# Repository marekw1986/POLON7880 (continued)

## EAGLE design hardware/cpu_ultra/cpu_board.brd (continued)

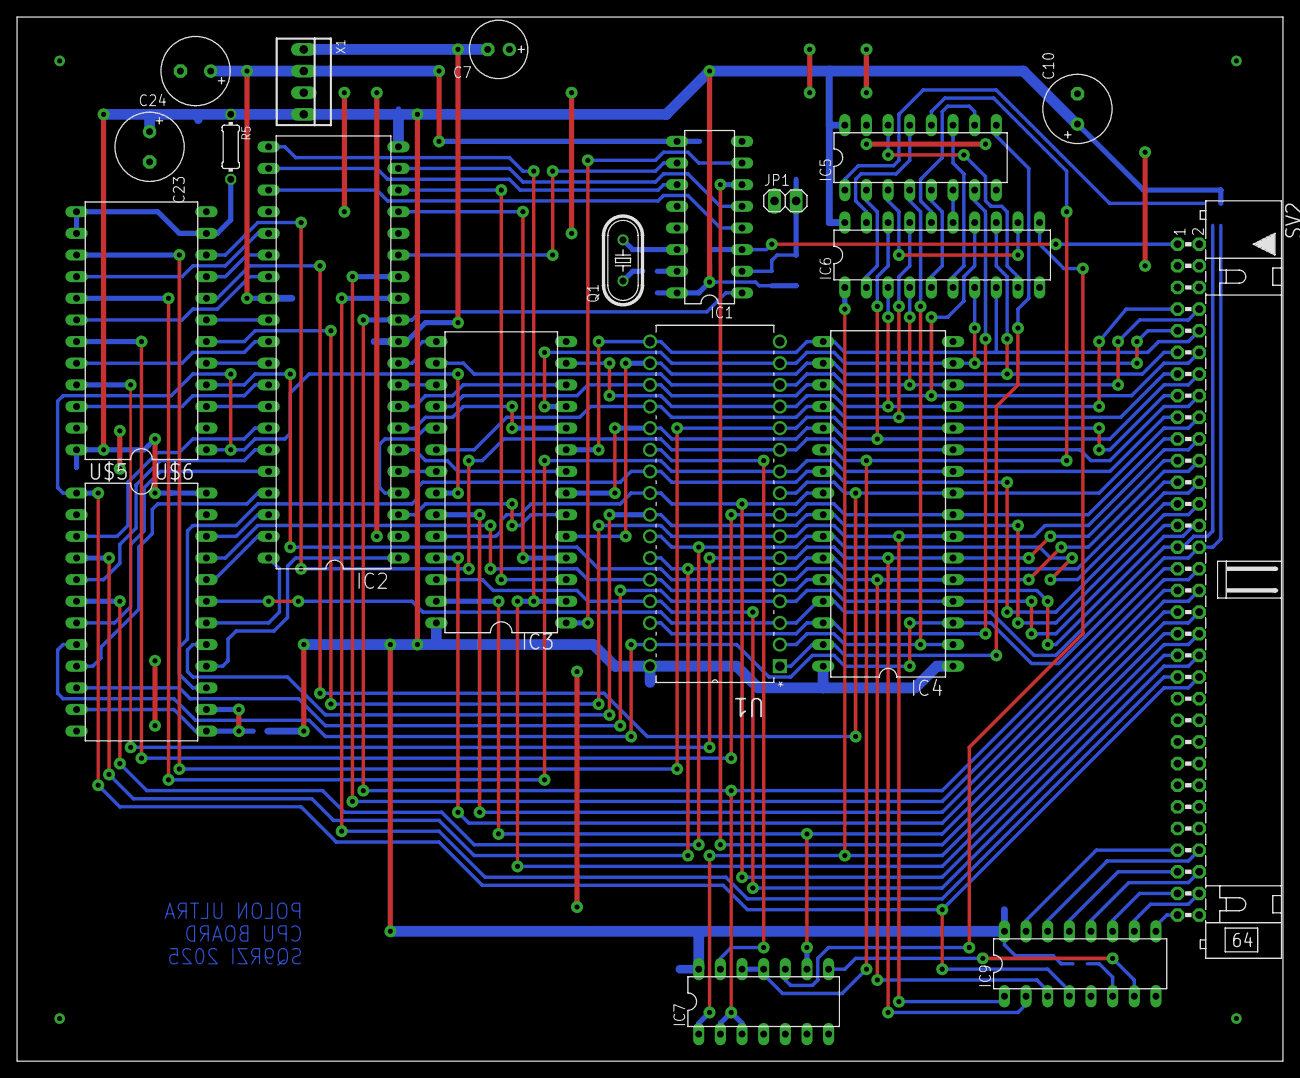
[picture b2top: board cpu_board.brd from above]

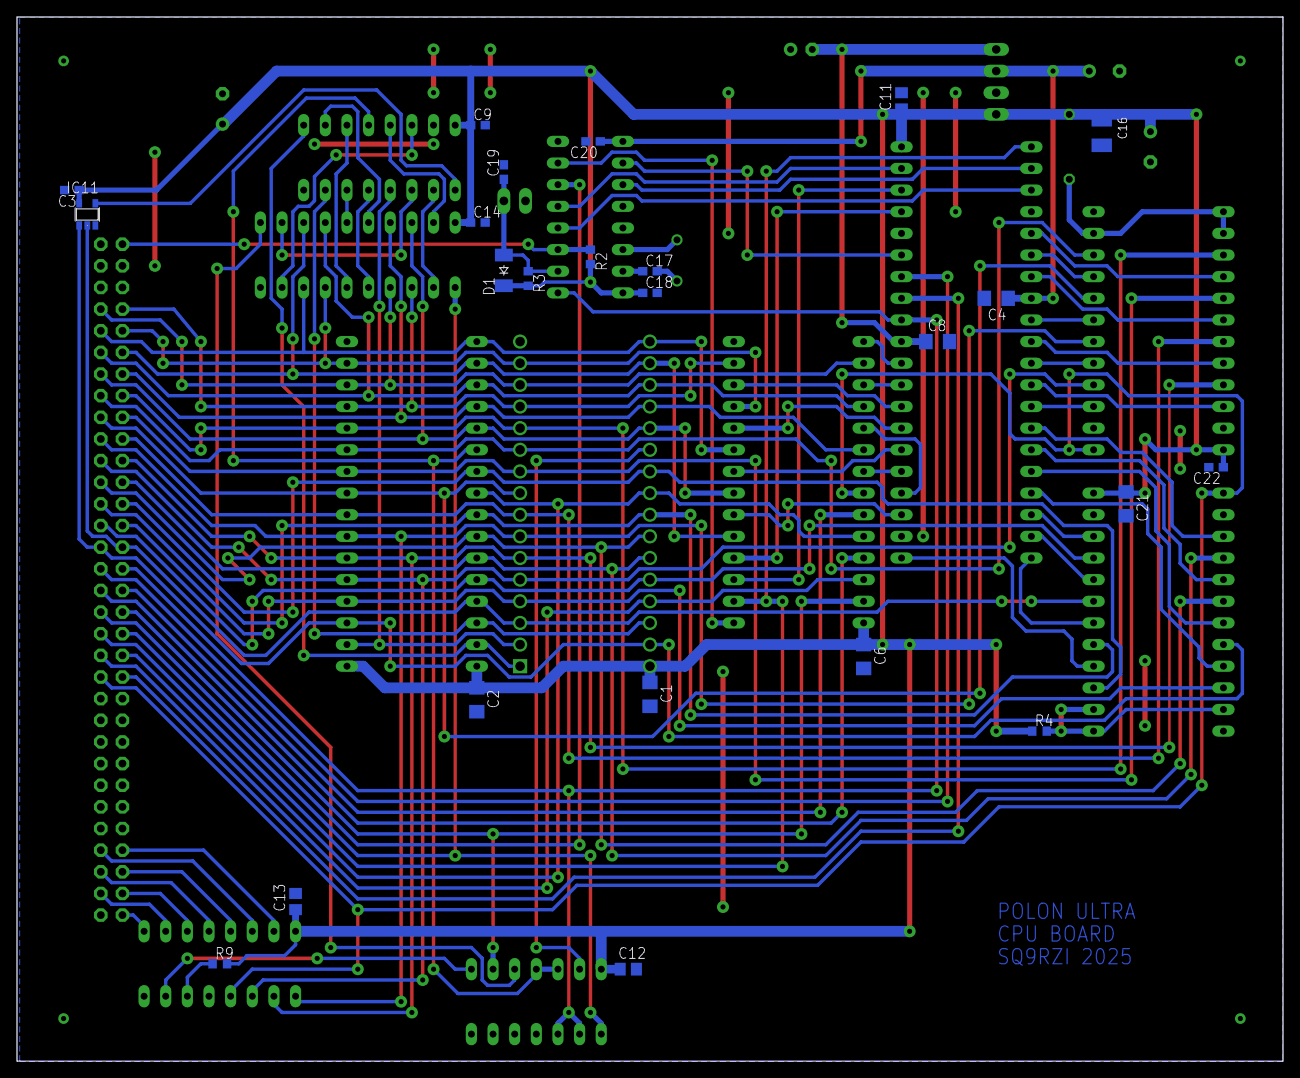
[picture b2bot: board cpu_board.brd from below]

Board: 2 copper layers, 148.6 x 122.5 mm, 44 parts (24 on the bottom side), 102 nets.

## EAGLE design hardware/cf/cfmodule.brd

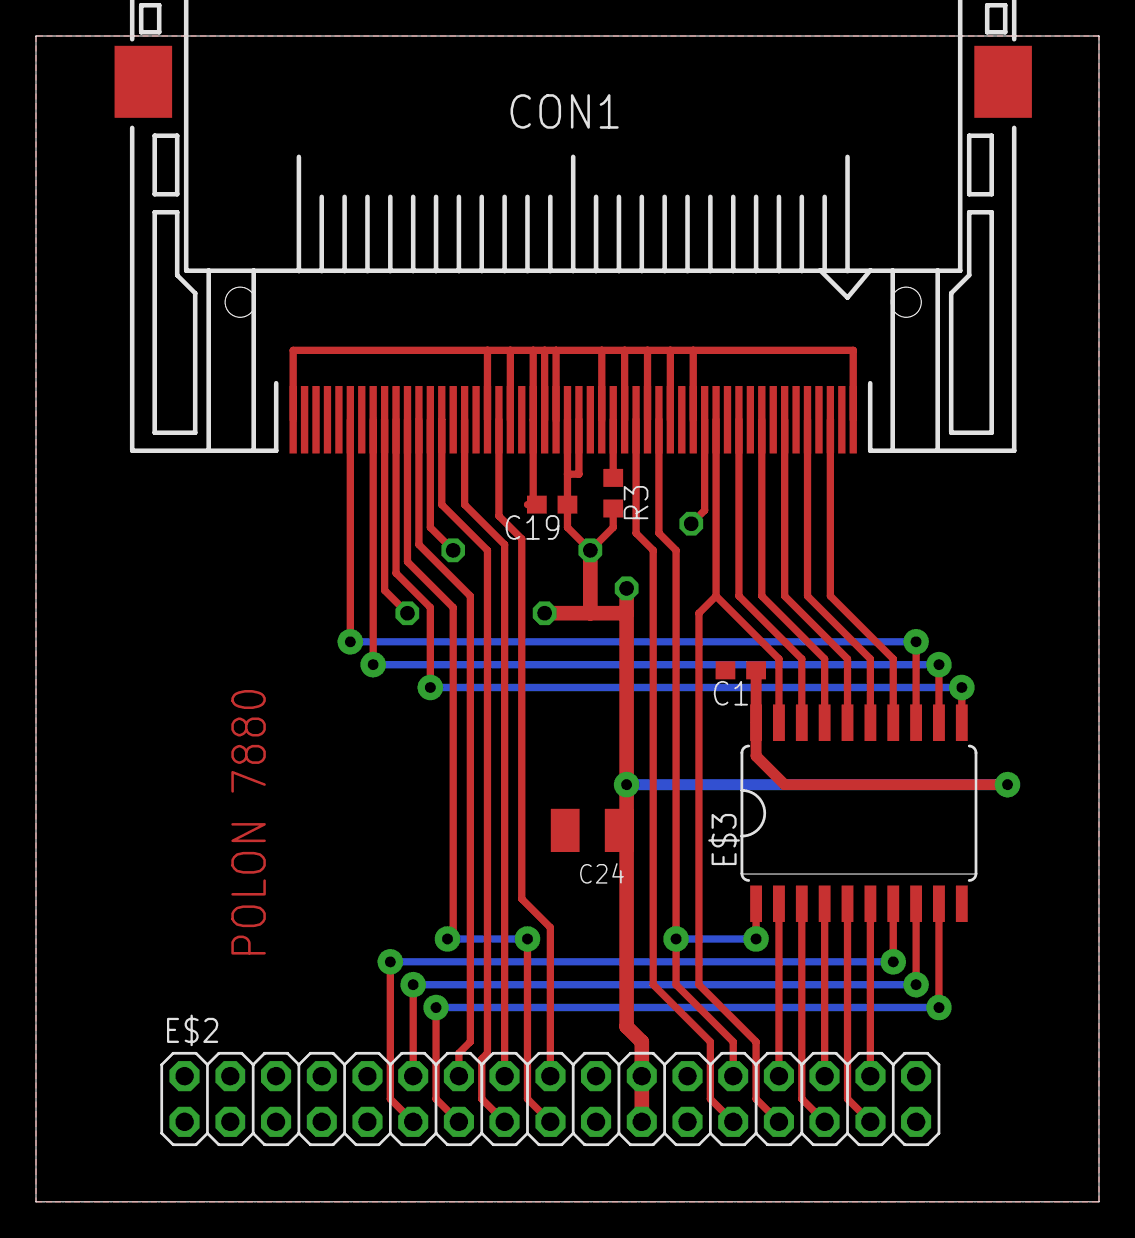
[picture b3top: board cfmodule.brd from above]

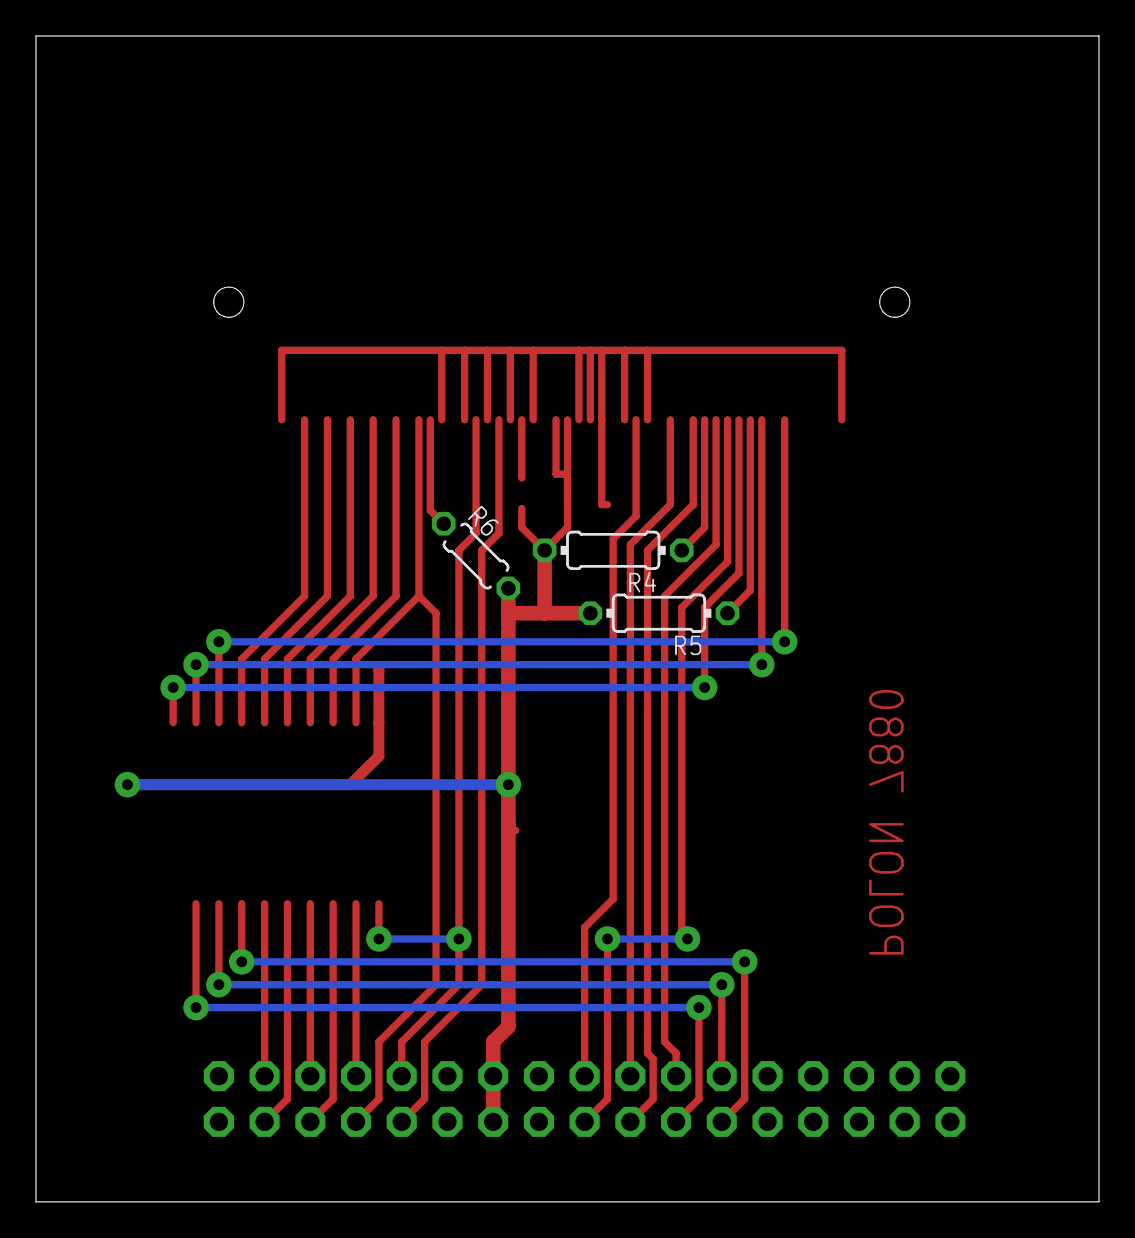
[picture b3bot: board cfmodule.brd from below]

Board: 2 copper layers, 59.1 x 64.8 mm, 10 parts (3 on the bottom side), 30 nets.

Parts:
C1, C19: C0603
C24: SMC_B
CON1: MI20-50PD-SF
E$2: 2X17
E$3: SO20W
R3: R0603
R4, R5: 0204/7
R6: 0204/5

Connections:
A0: CON1.20, E$2.14
A1: CON1.19, E$2.15
A2: CON1.18, E$2.16
CF_CS0: CON1.7, E$2.27, E$3.19
D0: CON1.21, E$3.11
D1: CON1.22, E$3.12
D2: CON1.23, E$3.13
D3: CON1.2, E$3.14
D4: CON1.3, E$3.15
D5: CON1.4, E$3.16
D6: CON1.5, E$3.17
D7: CON1.6, E$3.18
GND: C1.2, C19.2, C24.-, CON1.1, CON1.8, CON1.9, CON1.10, CON1.11, CON1.12, CON1.14, CON1.15, CON1.16, CON1.17, CON1.39, CON1.50, E$2.1, E$2.2, E$2.19, E$2.20, E$2.23, E$2.24, E$2.33, E$2.34, E$3.10
IO_RD: CON1.34, E$2.26, E$3.1
IO_WR: CON1.35, E$2.25
unnamed: CON1.36, R3.1
unnamed: CON1.44, R4.1
unnamed: CON1.46, R5.1
unnamed: CON1.32, R6.1
RST: CON1.41, E$2.18
S$1: E$2.30, E$3.4
S$2: E$2.28, E$3.2
S$8: E$2.13, E$3.9
S$9: CON1.45, E$2.17
S$11: E$2.29, E$3.3
S$12: E$2.31, E$3.5
S$13: E$2.32, E$3.6
S$15: E$2.12, E$3.8
S$16: E$2.11, E$3.7
VCC: C1.1, C19.1, C24.+, CON1.13, CON1.38, E$2.21, E$2.22, E$3.20, R3.2, R4.2, R5.2, R6.2

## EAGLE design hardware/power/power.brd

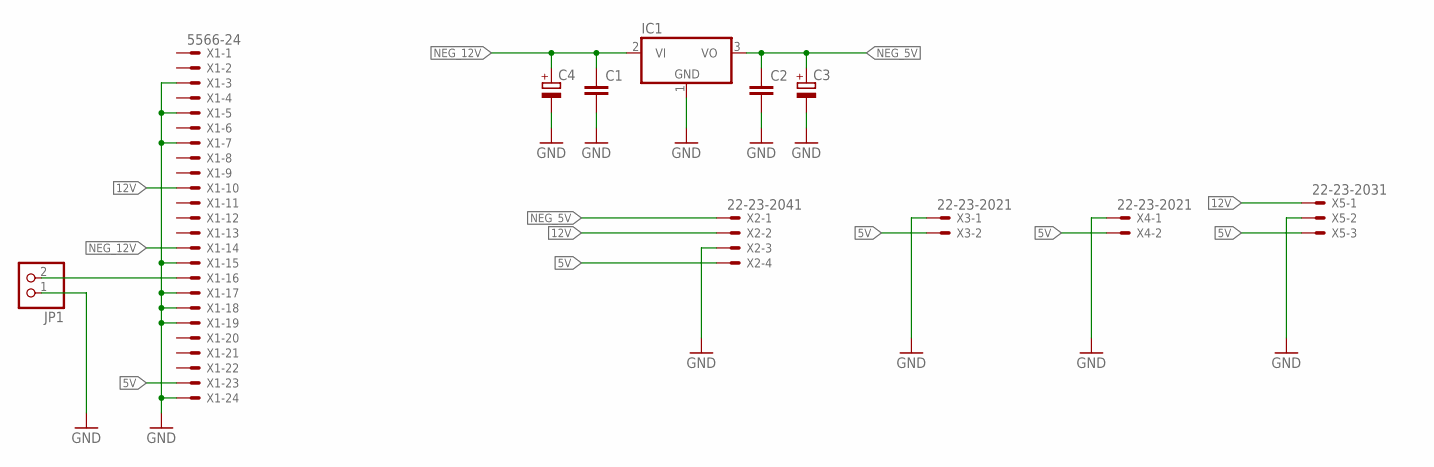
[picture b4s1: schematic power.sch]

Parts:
C1, C2: C-EUC1206; C1206
C3, C4: CPOL-EUSMCB; SMC_B
IC1: 7905T; TO220H
JP1: PINHD-1X2; 1X02
X1: 5566-24
X2: 22-23-2041
X3, X4: 22-23-2021
X5: 22-23-2031

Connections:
5V: X1.23, X2.4, X3.2, X4.2, X5.3
12V: X1.10, X2.2, X5.1
GND: C1.2, C2.2, C3.-, C4.-, IC1.1 (GND), JP1.1, X1.3, X1.5, X1.7, X1.15, X1.17, X1.18, X1.19, X1.24, X2.3, X3.1, X4.1, X5.2
unnamed: JP1.2, X1.16
NEG_5V: C2.1, C3.+, IC1.3 (VO), X2.1
NEG_12V: C1.1, C4.+, IC1.2 (VI), X1.14

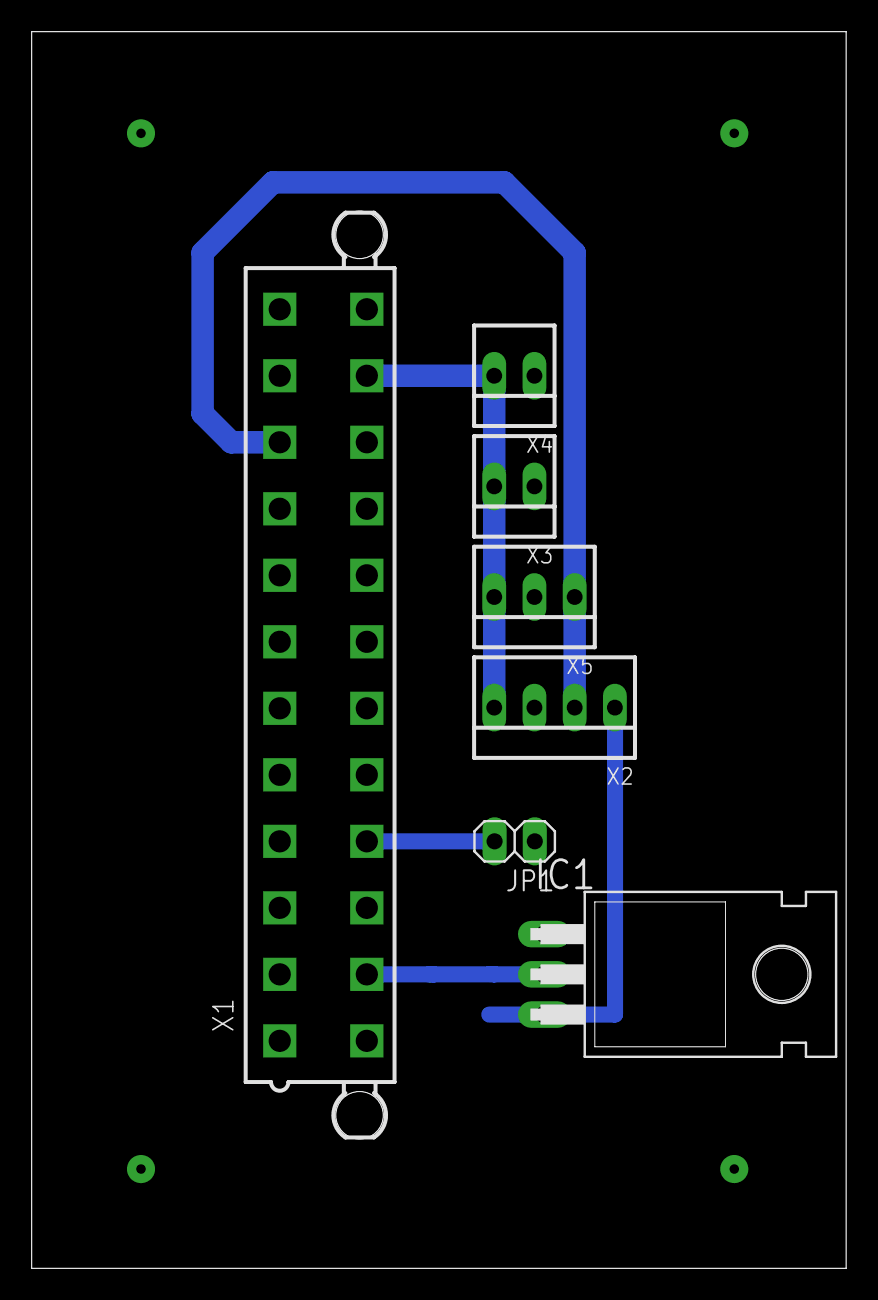
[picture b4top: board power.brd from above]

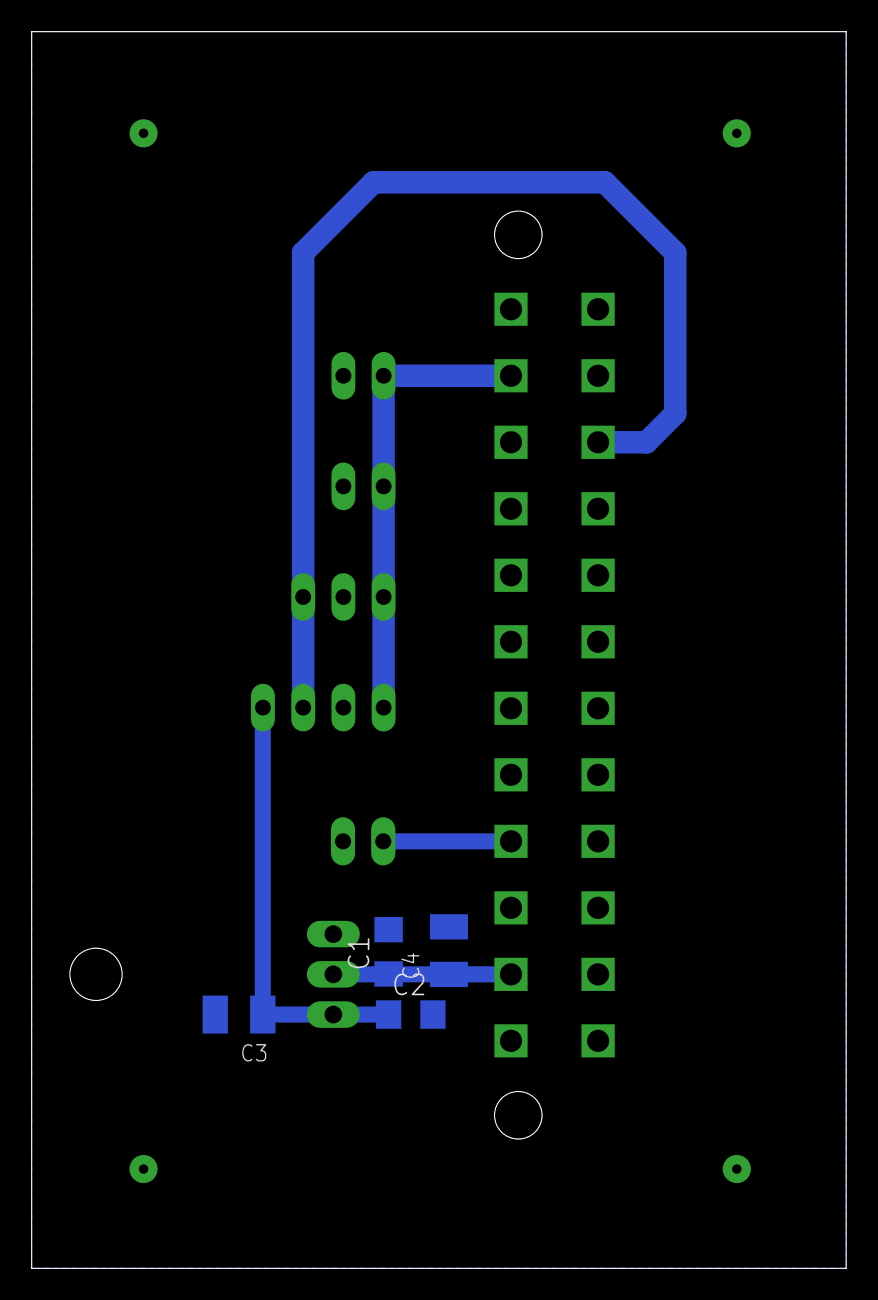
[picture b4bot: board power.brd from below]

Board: 2 copper layers, 51.4 x 78.1 mm, 11 parts (4 on the bottom side), 6 nets.

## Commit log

2020-08-27 README.md updated
2020-09-10 Some fixes
2020-09-18 PCB added
2020-09-22 Power board added
2020-09-24 Changed to fit current PCB version
2020-09-25 Bug fixed
2020-09-26 some changes
2020-09-27 hardware files rearanged
2020-09-27 pdf schematic added
2021-03-12 gitignore
2021-07-22 Minor chnges
2021-07-23 Interrupt test
2021-07-23 minor changes
2021-07-24 Dodana wersja prototypowa
2021-07-24 PCB project fixed
2021-07-24 PCB fixes
2021-08-02 Screen terminal
2021-08-04 Some chnges
2021-08-05 VDP screen
2021-08-07 Backspace works now
2023-09-05 changes in progress
2024-05-10 CF bootloader (work in progress)
2024-05-10 CF card info
2024-05-10 Printing CF info
2024-05-11 A little bit of cleaning
2024-05-11 Code moved to separate files
2024-05-11 Fonts and keyboard scancodes in separate files
2024-05-11 Better fonts added
2024-05-11 Hexdump (work in progress)
2024-05-11 minor update
2024-05-11 Small fix
2024-05-11 Hexdump works
2024-05-14 Printing partition table
2024-05-14 Loading code from partition 1 to RAM
2024-05-15 Boot menu added
2024-05-15 Check if MBR is proper
2024-05-15 typo fixed
2024-05-15 Checking MBR and partitio 1 before boot
2024-05-16 Detecting missing CF card
2024-05-20 Remove tinybasic dependencies from bootloader and utilities
2024-05-20 minor fix
2024-05-20 Loading 16kB from CF card and executing that code. Top RAM content with stack stack location adjusted
2024-05-20 Test code to lad and execute from CF card
2024-05-22 Minor updates
2024-05-25 Integrating bootloader with final hardware revision (work in progress
2024-06-04 VDP fix
2024-06-04 VDP updated
2024-06-05 VDP newline bug fixed
2024-06-07 Batter printing procedures
2024-06-18 CF module for prorotype
2024-06-18 CF module updated
2024-06-24 CPC16 routine added
2024-06-25 Hexdump RS232 routines added
2024-06-26 RS232 debug implemented
2024-07-09 Interrupt stack use iptimized
2024-07-09 Further optimizations
2025-01-01 Buffer added to D0..D7 lined of CF card
2025-01-03 Wronf CD card address in definitions.asm fixed
2025-01-03 CF card driver unified with tested prorotype version
2025-01-03 TinyBasic code unified with tested version from prototype hardware
2025-01-03 Utils modified
2025-01-03 Small fix in TinyBasic for prototype hardware
2025-01-03 CF indidator LED added to IO board
2025-02-01 CF card works on final version of hardware
2025-02-01 CP/M bios for final version of hardware added
2025-02-02 Memory organization changed to provide more RAM to CP/M
2025-02-09 Small changes in TB/Bootloader for final version
2025-02-09 CPM/Makefile for final version cleaned
2025-02-09 VDP cursor variables removed from TB/BL for final version
2025-02-09 Experiment with resizing RAM in final version
2025-02-09 Experiments with RAM resizing in final version. Changes in CP/M files
2025-02-12 Bug in memory address decoder fixed
2025-02-12 AEN signal connected to memory address decoder
2025-02-12 PCB optimized
2025-02-13 AEN removed from memory address decoder
2025-02-13 Direcotires rearanged, amount of code loaded during CP/M boot reduced
2025-02-14 Getting CP/M files automatically from GitHub locally if they do not exist locally
2025-02-14 Amount of data loaded during CP/M boot reduced
2025-02-14 Amount of data loaded at CP/M boot reduced also in prototype version
2025-02-14 prototype version stack fix
2025-03-15 CP/M for final version of hardware supports multiple partitions and writeable FS
2025-03-15 Changes ported from Z80 project
2025-03-15 Separate VDP buffer created
2025-03-15 Bug fixed in CF driver
2025-03-15 Bug fixed in CF driver (for final version)
2025-03-16 Added support for keyboart Ctrl codes
2025-03-16 Checking if bootloader loaded CP/M successfully
2025-03-17 Small refactoring
2025-03-18 ROM shadowing version
2025-03-19 ROM shadowed version of PCB modified
2025-03-19 Isolate pramaeter changeg in CPU board
2025-04-24 Final version moved to RAM shadowing
2025-04-24 TinyBasic removed from final version ROM
2025-04-24 CP/M bootloader added to replace old version of ROM (bootloader + TinyBasic)
2025-05-03 CPU board (ROM shadowing version) fix
2025-05-05 CPU board for ULTRA version (work in progress)
2025-05-05 ULTRA CPU board updatye
2025-05-05 Typo fix
2025-05-05 Several bugs fixed
2025-05-05 Minor bug fixed
2025-05-19 I/O board for ultra version (work in progress)
2025-05-19 I/O ultra board updated
2025-06-24 Ultra version added
2025-06-24 SCC2681 port addresses added
2025-06-24 Tx/Rx masks changed
2025-06-24 Code adapted to SCC2681 chip. Experimental version. Work in progress.
2025-06-24 Blink for final version modified
2025-06-24 UART code modified for ultra version
2025-08-23 Test UART for Ultra version added
2025-08-23 Leftover TinyBasic comment removed from bootloader code
2025-08-26 test_uart and blink for ultra version
2025-09-03 test_uart updated
2025-09-04 CP/M BIOS and bootloader for Ultra version
2025-09-11 MVI A, 00H replaced with XOR A to preserve memory and CPU cycles
2025-09-11 CPI 00H replaced with OR A
2025-09-11 Revert "CPI 00H replaced with OR A"
    This reverts commit 1968b9d18096c119c25759845871f29568eba181.
2025-09-11 Revert "MVI A, 00H replaced with XOR A to preserve memory and CPU cycles"
    This reverts commit 6d6722e1f909df7f7adef6c4b3d01f5aa4baf1e8.
2025-09-11 MVI A, 00H replaced with XRA A
2025-09-11 CPI 00H replaced with ORA A
2025-09-14 Bug in READ procedure fixed
2025-09-14 MVI A, 0 replaced with XRA A
2025-09-16 Minor optimizations
2025-09-23 Unused strings removed, CF related strings moved to cf.asm
2025-09-23 Unused strings removed, CF related strings moved to cf.asm (ultra version)
2025-09-24 I/O board (Ultra version) bug fixes
2026-06-22 Deffered writes fix
2026-06-25 Big fixed in PS2 keyboard driver, regrding handling Shift and Ctrl release
